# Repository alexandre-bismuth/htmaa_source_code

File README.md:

# HTMAA F26 Source Code

Welcome! 

This repository contains all of my source code for my weekly and final project of the "How to Make (Almost) Anything" class at MIT (Fall 26). It is organized per week, and is meant to be a collection of the entirety of the code written during this class.

For reference, you may want to visit the [class website](https://pub.cba.mit.edu/863.26/site/) as well as my [personal website for the class](https://pub.cba.mit.edu/863.26/alexandre.bismuth/index.html)!

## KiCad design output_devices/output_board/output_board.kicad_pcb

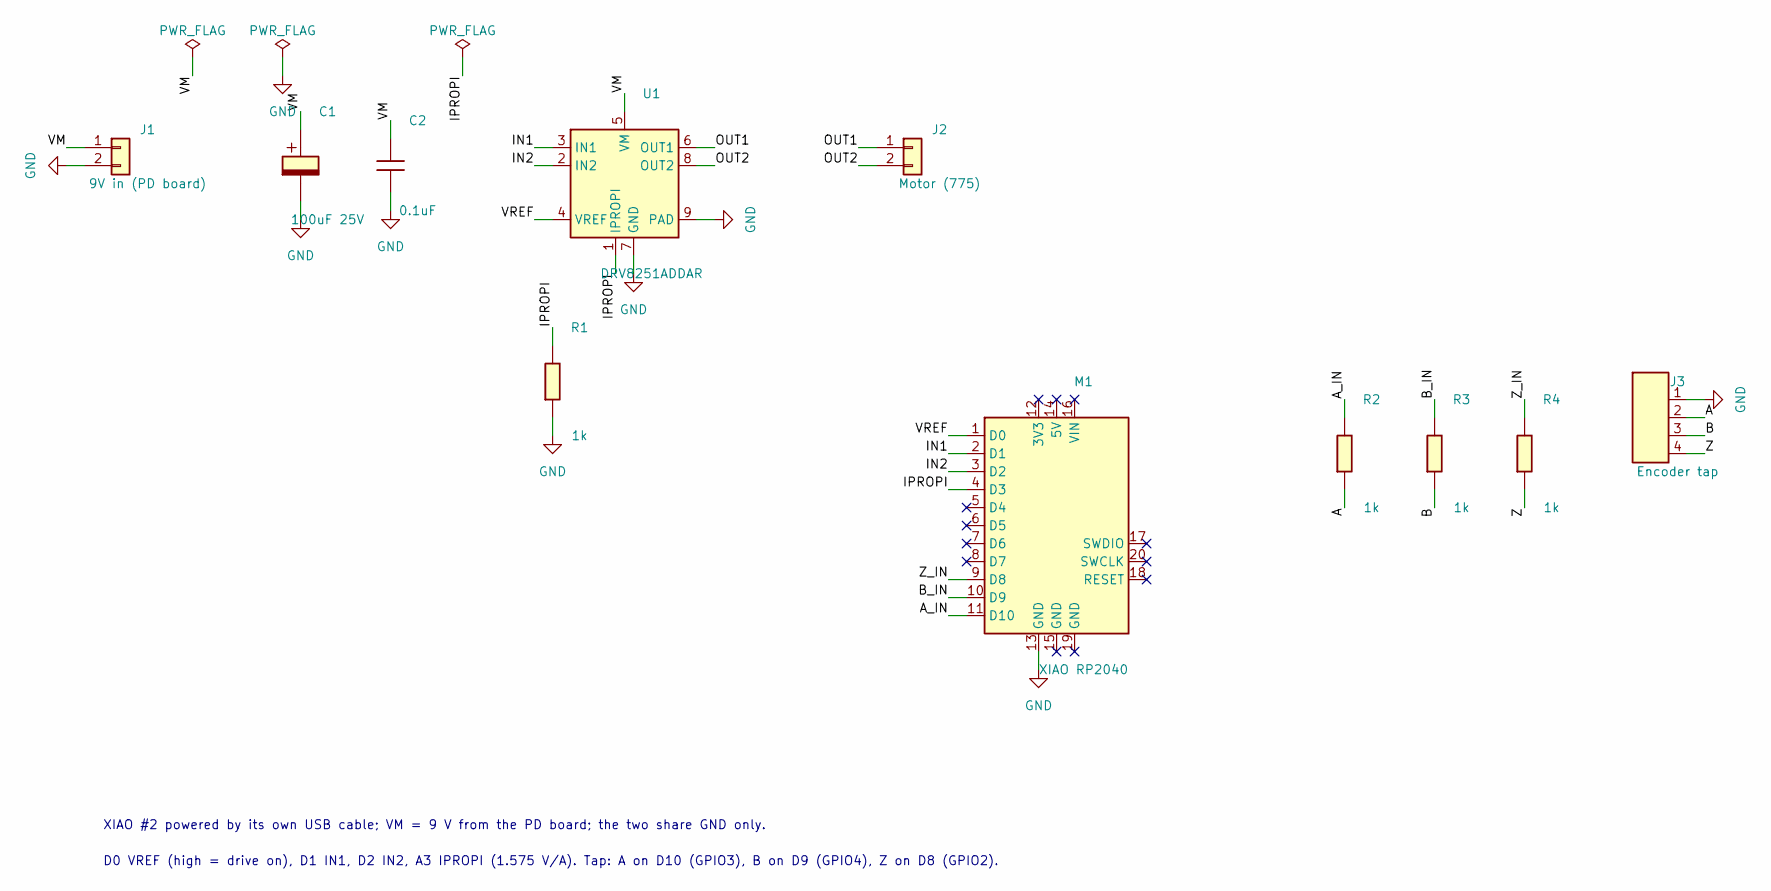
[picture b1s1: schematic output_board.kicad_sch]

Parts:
C1: 100uF 25V; CP_Elec_100uF_Panasonic_EEE-FN1E101UL
C2: 0.1uF; C_1206
J1: 9V in (PD board); Wire_Pads_Power
J2: Motor (775); Wire_Pads_Motor
J3: Encoder tap; JST_PH_B4B-PH-SM4-TB_1x04-1MP_P2.00mm_Vertical
M1: XIAO RP2040; XIAO_RP2040_SMD
R1, R2, R3, R4: 1k; R_1206
U1: DRV8251ADDAR; MotorDriver_HalfBridge_Texas_DRV8251ADDAR

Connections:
/A: J3.2, R2.2
/A_IN: M1.11 (D10), R2.1
/B: J3.3, R3.2
/B_IN: M1.10 (D9), R3.1
/IN1: M1.2 (D1), U1.3 (IN1)
/IN2: M1.3 (D2), U1.2 (IN2)
/IPROPI: M1.4 (D3), R1.1, U1.1 (IPROPI)
/OUT1: J2.1, U1.6 (OUT1)
/OUT2: J2.2, U1.8 (OUT2)
/VM: C1.1, C2.1, J1.1, U1.5 (VM)
/VREF: M1.1 (D0), U1.4 (VREF)
/Z: J3.4, R4.2
/Z_IN: M1.9 (D8), R4.1
GND: C1.2, C2.2, J1.2, J3.1, M1.13 (GND), R1.2, U1.7 (GND), U1.9 (PAD)

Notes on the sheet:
XIAO #2 powered by its own USB cable; VM = 9 V from the PD board; the two share GND only.
D0 VREF (high = drive on), D1 IN1, D2 IN2, A3 IPROPI (1.575 V/A). Tap: A on D10 (GPIO3), B on D9 (GPIO4), Z on D8 (GPIO2).

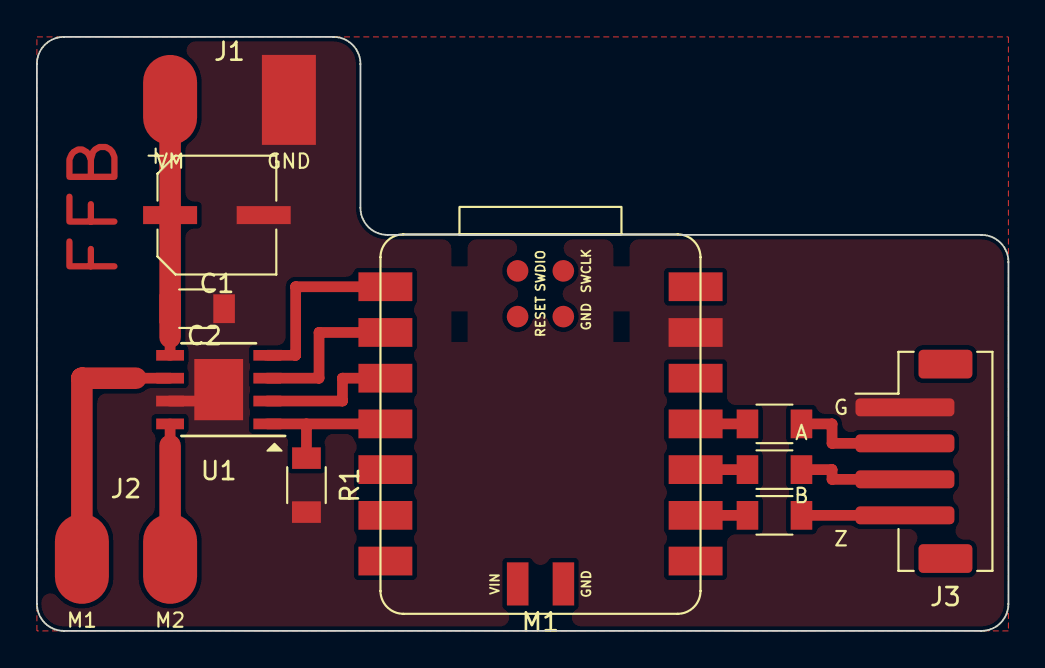
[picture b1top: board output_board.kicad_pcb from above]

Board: 2 copper layers, 54.0 x 33.0 mm, 11 parts (0 on the bottom side), 14 nets.

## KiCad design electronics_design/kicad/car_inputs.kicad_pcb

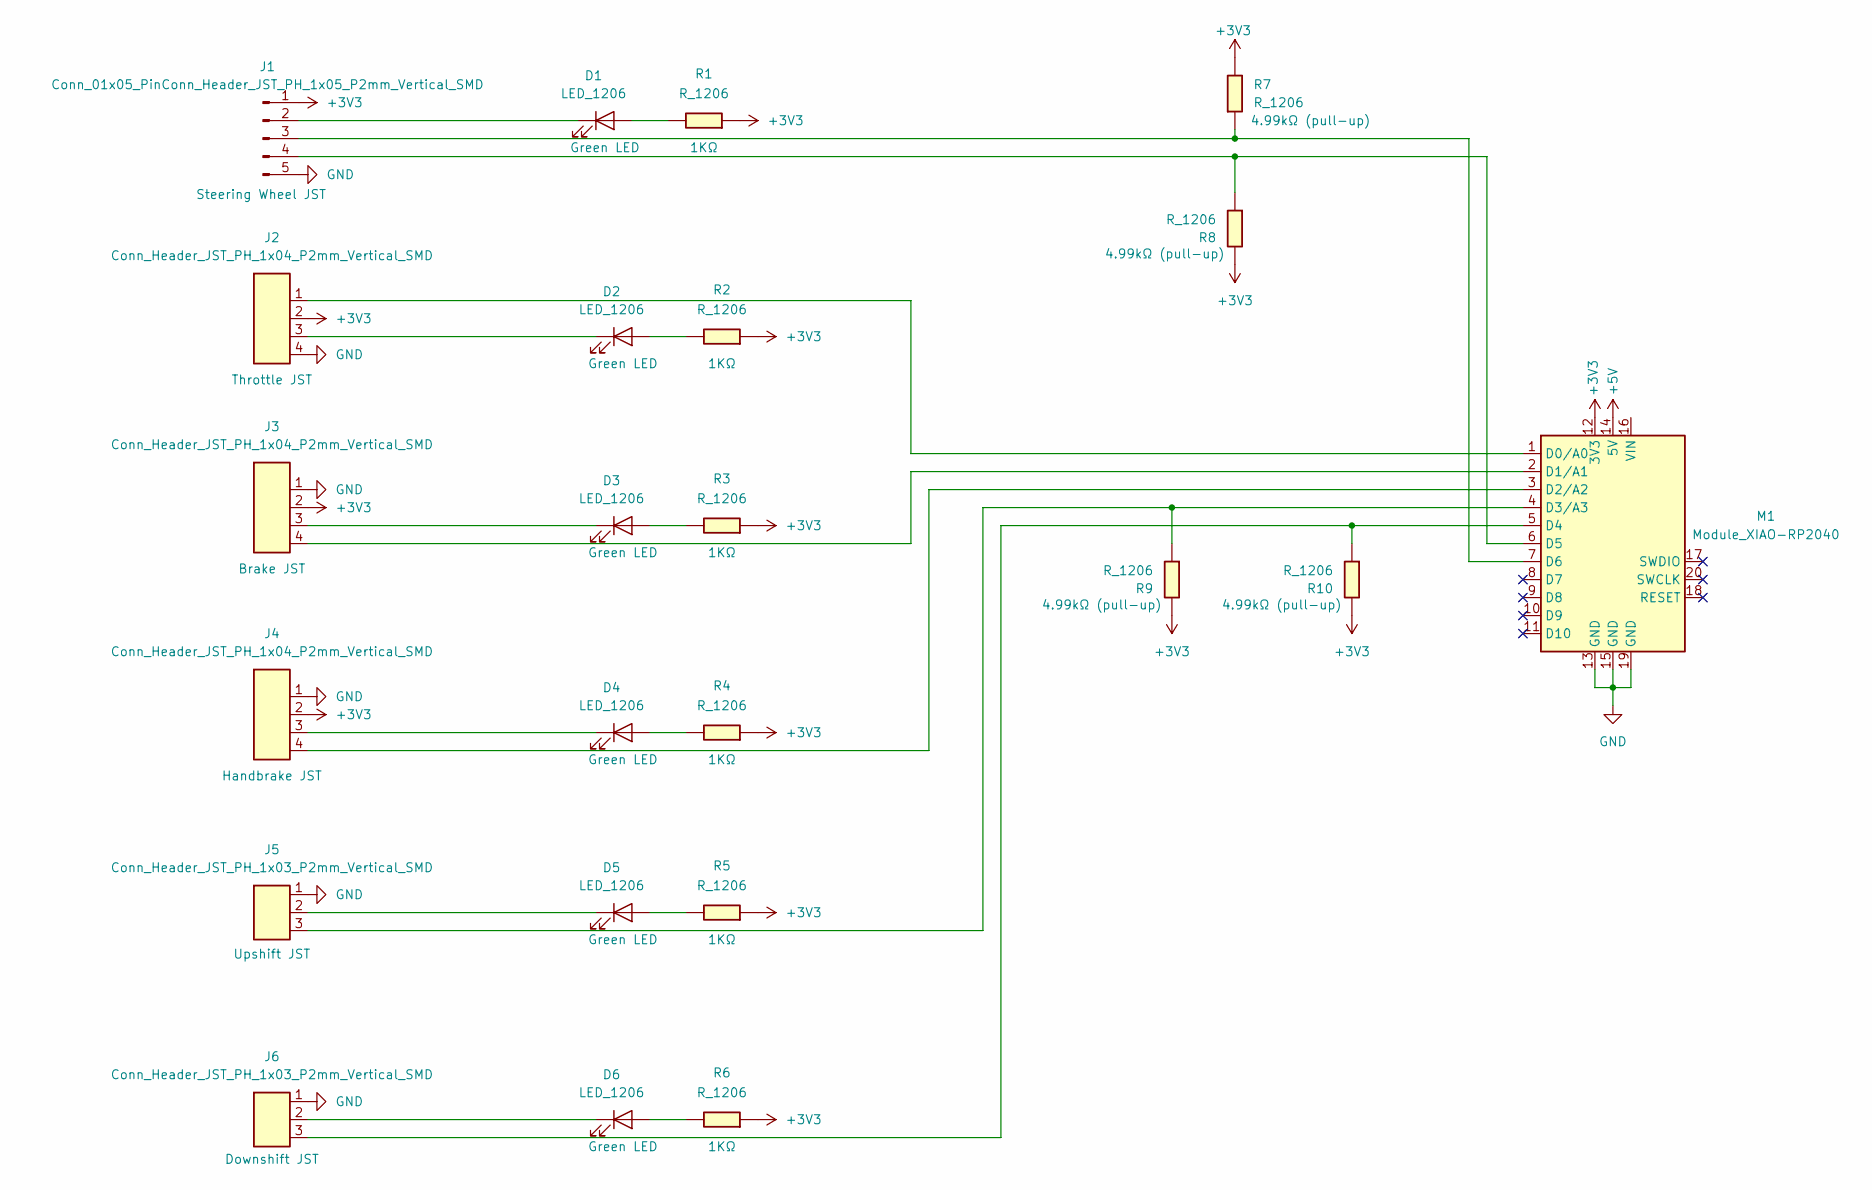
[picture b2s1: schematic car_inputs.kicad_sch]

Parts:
D1, D2, D3, D4, D5, D6: LED_1206
J1: Conn_01x05_PinConn_Header_JST_PH_1x05_P2mm_Vertic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; JST_PH_B5B-PH-SM4-TB_1x05-1MP_P2.00mm_Vertical
J2, J3, J4: Conn_Header_JST_PH_1x04_P2mm_Vertical_SMD; Header_JST_PH_1x04_P2mm_Vertical_SMD
J5, J6: Conn_Header_JST_PH_1x03_P2mm_Vertical_SMD; Header_JST_PH_1x03_P2mm_Vertical_SMD
M1: Module_XIAO-RP2040; SeeedStudio_XIAO_RP2040
R1, R2, R3, R4, R5, R6, R7, R8, R9, R10: R_1206

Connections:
+3V3: J1.1, J2.2, J3.2, J4.2, M1.12 (3V3), R1.2, R2.2, R3.2, R4.2, R5.2, R6.2, R7.1, R8.1, R9.1, R10.1
+5V: M1.14 (5V)
GND: J1.5, J2.4, J3.1, J4.1, J5.1, J6.1, M1.13 (GND), M1.15 (GND), M1.19 (GND)
unnamed: D1.2 (A), R1.1
unnamed: D1.1 (K), J1.2
unnamed: D2.2 (A), R2.1
unnamed: D2.1 (K), J2.3
unnamed: D3.2 (A), R3.1
unnamed: D3.1 (K), J3.3
unnamed: D4.2 (A), R4.1
unnamed: D4.1 (K), J4.3
unnamed: D5.2 (A), R5.1
unnamed: D5.1 (K), J5.2
unnamed: D6.2 (A), R6.1
unnamed: D6.1 (K), J6.2
unnamed: J1.3, M1.7 (D6), R7.2
unnamed: J1.4, M1.6 (D5), R8.2
unnamed: J2.1, M1.1 (D0/A0)
unnamed: J3.4, M1.2 (D1/A1)
unnamed: J4.4, M1.3 (D2/A2)
unnamed: J5.3, M1.4 (D3/A3), R9.2
unnamed: J6.3, M1.5 (D4), R10.2

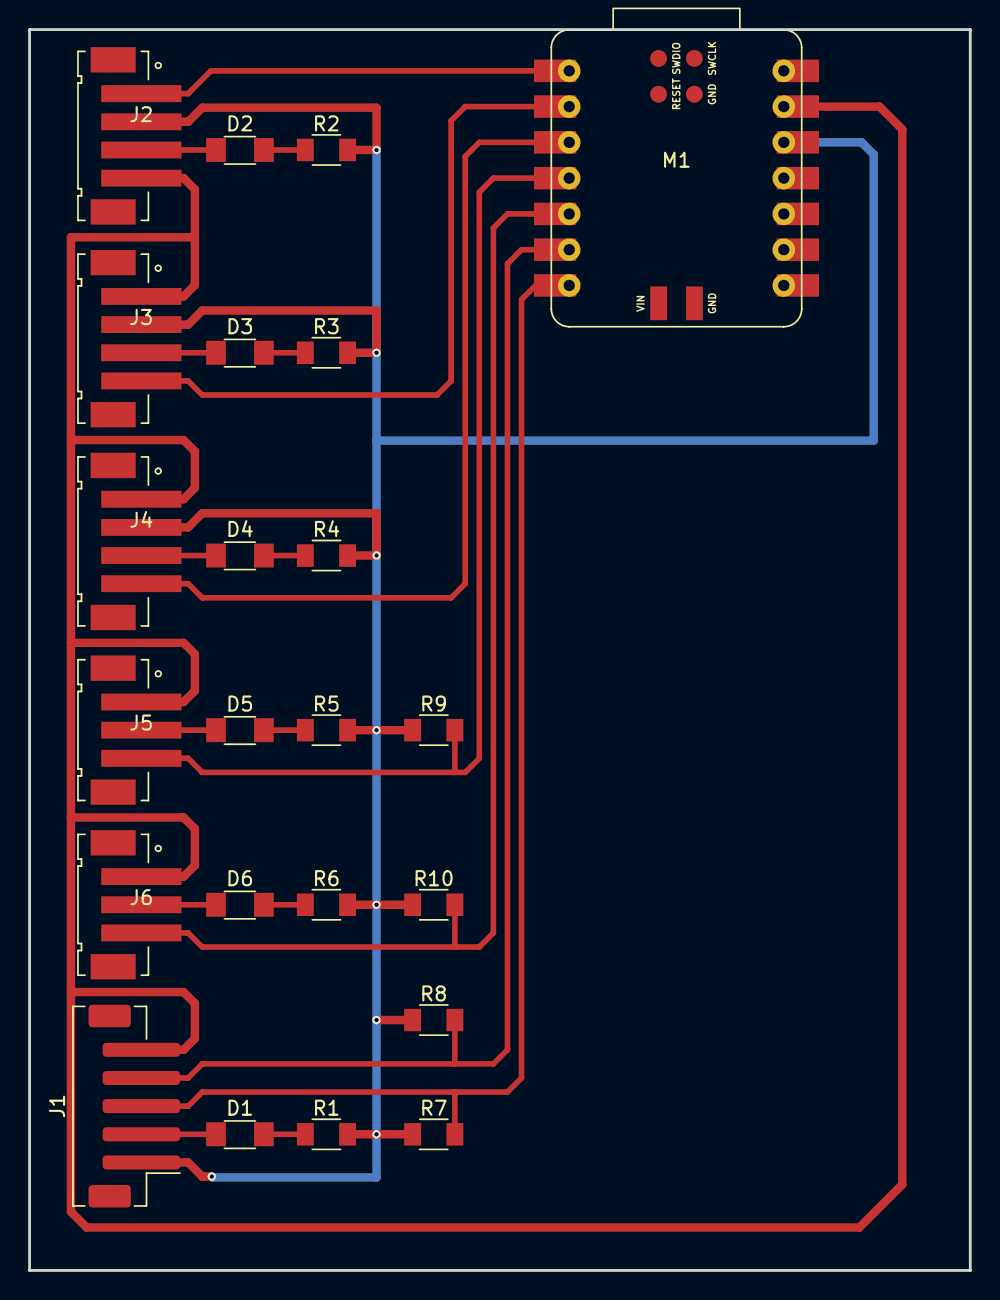
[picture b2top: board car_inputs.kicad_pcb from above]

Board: 2 copper layers, 66.8 x 88.1 mm, 23 parts (0 on the bottom side), 21 nets.
